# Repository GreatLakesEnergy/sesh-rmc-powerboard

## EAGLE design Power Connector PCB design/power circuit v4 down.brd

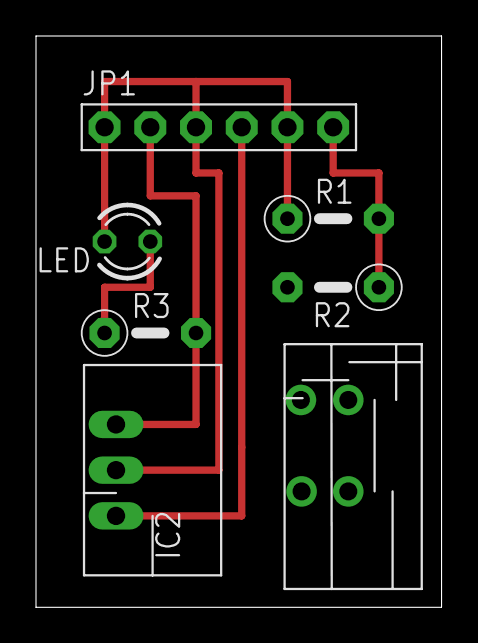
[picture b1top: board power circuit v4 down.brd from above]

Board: 2 copper layers, 22.5 x 31.7 mm, 7 parts (0 on the bottom side), 5 nets.

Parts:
IC2: 7812TV; TO220V
JP1: 1X06-BIG
LED: TLLR4400; LED3MM
R1: 1.2K; 0207/5V
R2: 10K; 0207/5V
R3: 1K; 0207/5V
X1: 1789650

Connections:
24V: IC2.1, JP1.4
A5: JP1.6, R1.2, R2.1
GND: IC2.2, JP1.1, JP1.3, JP1.5, LED.K, R1.1
unnamed: LED.A, R3.1
unnamed: IC2.3, JP1.2, R3.2

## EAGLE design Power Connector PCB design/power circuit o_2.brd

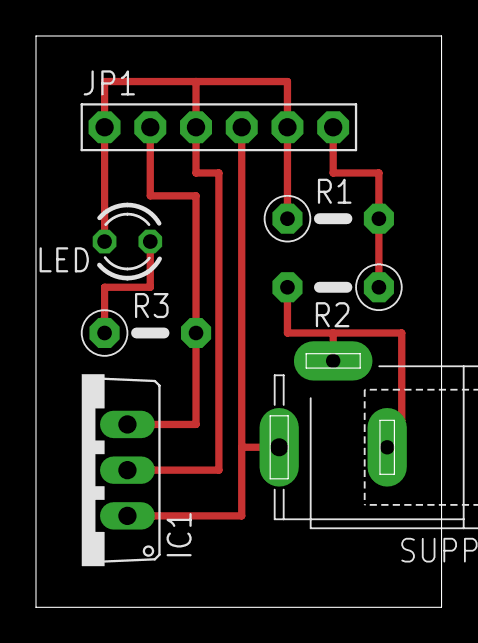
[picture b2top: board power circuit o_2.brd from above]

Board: 2 copper layers, 22.5 x 31.7 mm, 7 parts (0 on the bottom side), 6 nets.

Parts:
IC1: 7824TV; TO220V
JP1: 1X06-BIG
LED: TLLR4400; LED3MM
R1: 1.2K; 0207/5V
R2: 10K; 0207/5V
R3: 1K; 0207/5V
SUPPLY: SPC4078

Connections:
24V: IC1.1, JP1.4, SUPPLY.3
A5: JP1.6, R1.2, R2.1
GND: IC1.2, JP1.1, JP1.3, JP1.5, LED.K, R1.1
unnamed: LED.A, R3.1
unnamed: IC1.3, JP1.2, R3.2
unnamed: R2.2, SUPPLY.1, SUPPLY.2

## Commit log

2016-06-27 adding several iterations of the power board PCB. Finished version with power jack then modification with a few details to fix with clip-terminals
2016-06-27 deleting folder
